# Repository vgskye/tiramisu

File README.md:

# Tiramisu!
SlimeVR-like full-body trackers using nRF52840 and LSM6DSV.

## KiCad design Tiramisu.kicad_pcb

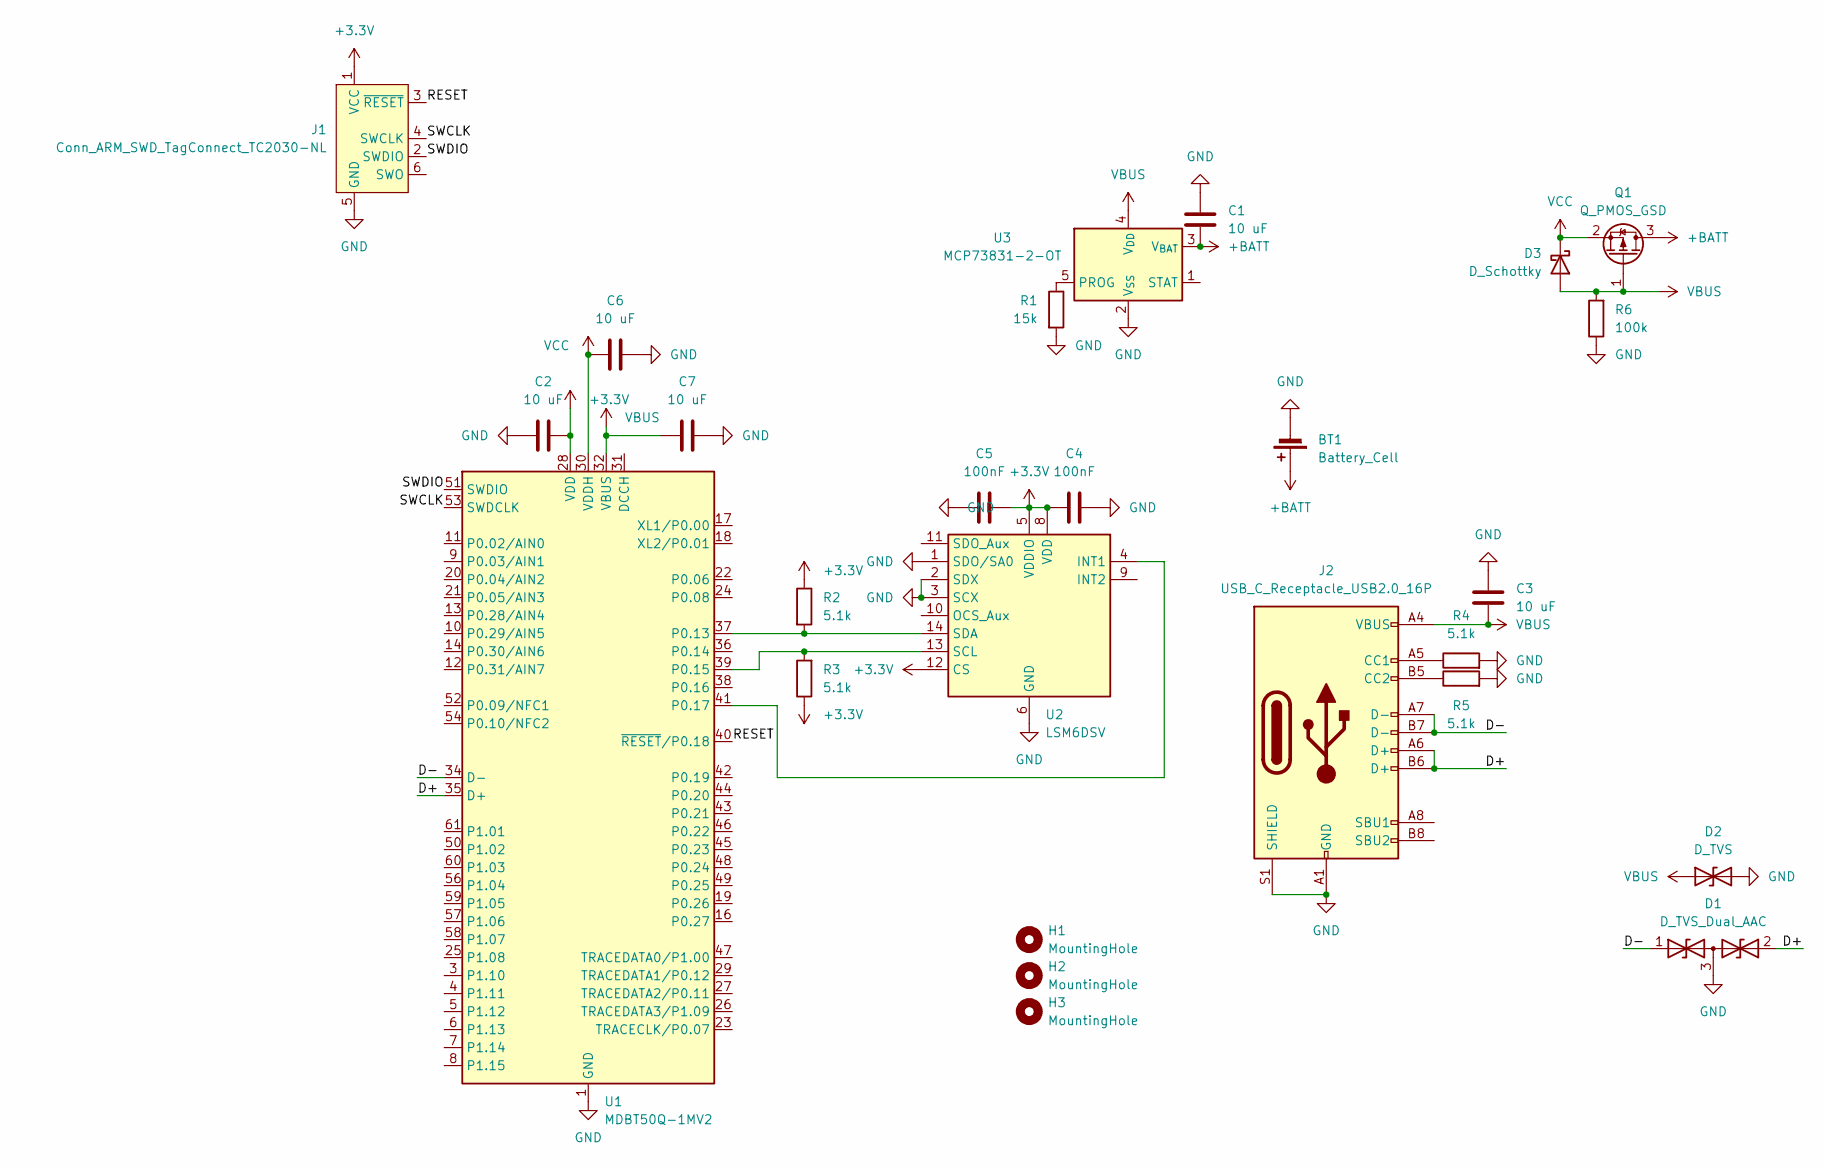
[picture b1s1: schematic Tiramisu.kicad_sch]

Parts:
BT1: Battery_Cell; Molex_Pico-EZmate_78171-0002_1x02-1MP_P1.20mm_Vertical
C1, C2, C3, C6, C7: 10 uF; C_0603_1608Metric
C4, C5: 100nF; C_0603_1608Metric
D1: D_TVS_Dual_AAC; SOT-23_AltChevron
D2: D_TVS; D_0603_1608Metric
D3: D_Schottky; D_0603_1608Metric
H1, H2, H3: MountingHole; MountingHole_1.7mm_M1.6
J1: Conn_ARM_SWD_TagConnect_TC2030-NL; Tag-Connect_TC2030-IDC-NL_2x03_P1.27mm_Vertical
J2: USB_C_Receptacle_USB2.0_16P; USB_C_Receptacle_JAE_DX07S016JA1R1500_alt
Q1: Q_PMOS_GSD; SOT-23
R1: 15k; R_0603_1608Metric
R2, R3, R4, R5: 5.1k; R_0603_1608Metric
R6: 100k; R_0603_1608Metric
U1: MDBT50Q-1MV2; Raytac_MDBT50Q
U2: LSM6DSV; LGA-14_3x2.5mm_P0.5mm_LayoutBorder3x4y
U3: MCP73831-2-OT; SOT-23-5

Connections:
+3.3V: C2.2, C4.2, C5.2, J1.1 (VCC), R2.1, R3.1, U1.28 (VDD), U2.5 (VDDIO), U2.8 (VDD), U2.12 (CS)
+BATT: BT1.1 (+), C1.1, Q1.3 (D), U3.3 (V_{BAT})
/D+: D1.2 (A2), J2.A6 (D+), J2.B6 (D+), U1.35 (D+)
/D-: D1.1 (A1), J2.A7 (D-), J2.B7 (D-), U1.34 (D-)
/RESET: J1.3 (~RESET), U1.40 (~RESET/P0.18)
/SWCLK: J1.4 (SWCLK), U1.53 (SWDCLK)
/SWDIO: J1.2 (SWDIO), U1.51 (SWDIO)
GND: BT1.2 (-), C1.2, C2.1, C3.1, C4.1, C5.1, C6.1, C7.2, D1.3 (common), D2.2 (A2), J1.5 (GND), J2.A1 (GND), J2.A12 (GND), J2.B1 (GND), J2.B12 (GND), J2.S1 (SHIELD), R1.2, R4.2, R5.2, R6.1, U1.1 (GND), U1.2 (GND), U1.15 (GND), U1.33 (GND), U1.55 (GND), U2.1 (SDO/SA0), U2.2 (SDX), U2.3 (SCX), U2.6 (GND), U2.7 (GND), U3.2 (V_{SS})
unnamed: J2.A5 (CC1), R4.1
unnamed: J2.B5 (CC2), R5.1
unnamed: R2.2, U1.37 (P0.13), U2.14 (SDA)
unnamed: R3.2, U1.39 (P0.15), U2.13 (SCL)
unnamed: U1.41 (P0.17), U2.4 (INT1)
unnamed: R1.1, U3.5 (PROG)
VBUS: C3.2, C7.1, D2.1 (A1), D3.2 (A), J2.A4 (VBUS), J2.A9 (VBUS), J2.B4 (VBUS), J2.B9 (VBUS), Q1.1 (G), R6.2, U1.32 (VBUS), U3.4 (V_{DD})
VCC: C6.2, D3.1 (K), Q1.2 (S), U1.30 (VDDH)

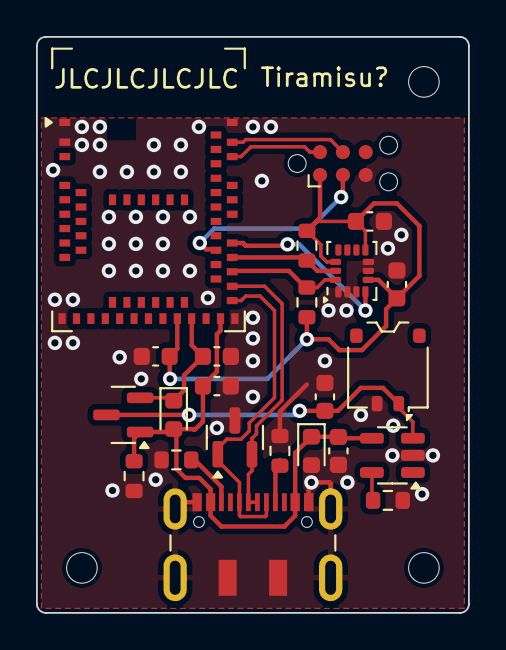
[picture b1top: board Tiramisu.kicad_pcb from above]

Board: 2 copper layers, 24.0 x 32.0 mm, 26 parts (0 on the bottom side), 16 nets.

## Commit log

2024-04-20 asdf
2024-04-22 that should be a +3V3 route oops
2024-04-23 final export
2025-03-30 Create LICENSE
